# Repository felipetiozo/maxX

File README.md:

# maxX
Braço Robótico para fins educacionais
<div style="align=middle"></div>
<p align="center";> <b> Dia de testes do braço </b> </p>

# Divisões do projeto
* [`Software`](https://github.com/felipetiozo/maxX/tree/master/Software): Contem todas bibliotecas e código final do braço.
* [`Eletronica`](https://github.com/felipetiozo/maxX/tree/master/Eletronica): Possui todo esquema eletronico e o modelo final da PCB.
* [`Mecânica`](https://github.com/felipetiozo/maxX/tree/master/Mecanica): Todos arquivos .sldprt e .dxf do projeto.

## Eletronica
A PCB (Printed board circuit) do projeto foi construida no software [EAGLE(v8.3.1)](https://www.autodesk.com/products/eagle/overview) e fresada em uma mini cnc. [(Othermill)](https://www.bantamtools.com/)
### Lista de materiais 
| Qtd | Item | Loja | R$ |
|-----|------|-----|-----|
| 6 | MG995 Servo Motor | [Jsumo](http://www.jsumo.com/mg995-metal-gear-rc-servo-motor-towerpro) | 30,00 | 
| 1 | ATmega328P | [B.E](http://www.baudaeletronica.com.br/kit-arduino-atmega328p-bootloader.html) | 17,81 | 
| 2 | Encoder Decoder KY-040 | [Robocore](https://www.pololu.com/product/713) | 11,00 | 
| 1 | LCD 16x2 i2c | [Robocore](https://www.robocore.net/loja/produtos/lcd-16x2-5v-com-interface-i2c.html) | 49,00 | 
| 1 | FTDI Basic Breakout - 3.3V | [Sparkfun](https://www.sparkfun.com/products/9873) | 38,00 | 
| 2 | LM2596 | [B.E](http://www.baudaeletronica.com.br/modulo-regulador-de-tensao-lm2596.html) | 10,97 | 
| 1 | Fonte 12V 3A | [B.E](http://www.baudaeletronica.com.br/fonte-chaveada-12vdc-3a.html) | 48,37 | 

## Mecânica
O projeto mecânico foi desenvolvido no software de CAD [SolidWorks](http://www.solidworksbrasil.com.br/) e foi construido em 5 versões até chegar a final. Todas as peças foram impressas em 3D e cortadas em máquinas de corte a laser.

### Lista de materiais
| Qtd | Item | Loja | R$ |
|-----|------|-----|-----|
| 1 | Garra Robótica Croc | [Robocore](https://www.robocore.net/loja/produtos/garra-robotica-croc.html) | 29,00 | 
| 2 | Ball Caster with 3/8″ Metal Ball | [Pololu](https://www.pololu.com/product/951) | 6,50 | 

## Software
O software foi desenvolvido em cima da IDE [Arduino](https://www.arduino.cc/) e está dividido em diversas funções para uma utilização mais fácil.

# Contribuidores

<div style="align=middle"></div>
<p align="center";> <b> Participantes do grupo </b> </p>

* [Felipe Tiozo](https://github.com/felipetiozo)
* [Igor Sousa](https://www.linkedin.com/in/igorsousa/)
* [Guilherme Basilio](https://www.facebook.com/guilherme.basilio.969)
* [Carlos Lima](https://www.facebook.com/profile.php?id=100004150566418)

## Agradecimentos
* [Engenhoteca](http://engenhoteca.com.br/)
* [João Pedro](https://github.com/joaopedrovbs)
* [Felipe Silva](https://github.com/feosilva)
* [Marcos Oliveira](https://github.com/marcosdeoliveira)
* [Tenda Digital](http://tenda.digital/)

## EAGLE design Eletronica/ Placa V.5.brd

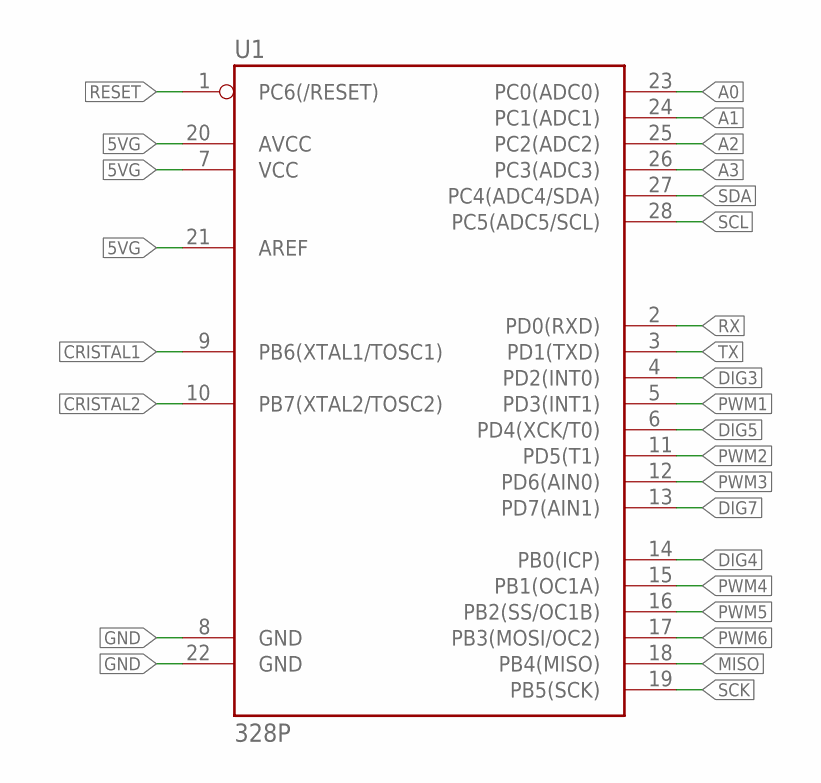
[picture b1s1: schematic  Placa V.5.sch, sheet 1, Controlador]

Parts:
U1: 328P; DIP28

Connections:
5VG: U1.7 (VCC), U1.20 (AVCC), U1.21 (AREF); also elsewhere on the board
A0: U1.23 (PC0(ADC0)); also elsewhere on the board
A1: U1.24 (PC1(ADC1)); also elsewhere on the board
A2: U1.25 (PC2(ADC2)); also elsewhere on the board
A3: U1.26 (PC3(ADC3)); also elsewhere on the board
CRISTAL1: U1.9 (PB6(XTAL1/TOSC1)); also elsewhere on the board
CRISTAL2: U1.10 (PB7(XTAL2/TOSC2)); also elsewhere on the board
DIG3: U1.4 (PD2(INT0)); also elsewhere on the board
DIG4: U1.14 (PB0(ICP)); also elsewhere on the board
DIG5: U1.6 (PD4(XCK/T0)); also elsewhere on the board
DIG7: U1.13 (PD7(AIN1)); also elsewhere on the board
GND: U1.8 (GND), U1.22 (GND); also elsewhere on the board
MISO: U1.18 (PB4(MISO))
PWM1: U1.5 (PD3(INT1)); also elsewhere on the board
PWM2: U1.11 (PD5(T1)); also elsewhere on the board
PWM3: U1.12 (PD6(AIN0)); also elsewhere on the board
PWM4: U1.15 (PB1(OC1A)); also elsewhere on the board
PWM5: U1.16 (PB2(SS/OC1B)); also elsewhere on the board
PWM6: U1.17 (PB3(MOSI/OC2)); also elsewhere on the board
RESET: U1.1 (PC6(/RESET)); also elsewhere on the board
RX: U1.2 (PD0(RXD)); also elsewhere on the board
SCK: U1.19 (PB5(SCK)); also elsewhere on the board
SCL: U1.28 (PC5(ADC5/SCL)); also elsewhere on the board
SDA: U1.27 (PC4(ADC4/SDA)); also elsewhere on the board
TX: U1.3 (PD1(TXD)); also elsewhere on the board

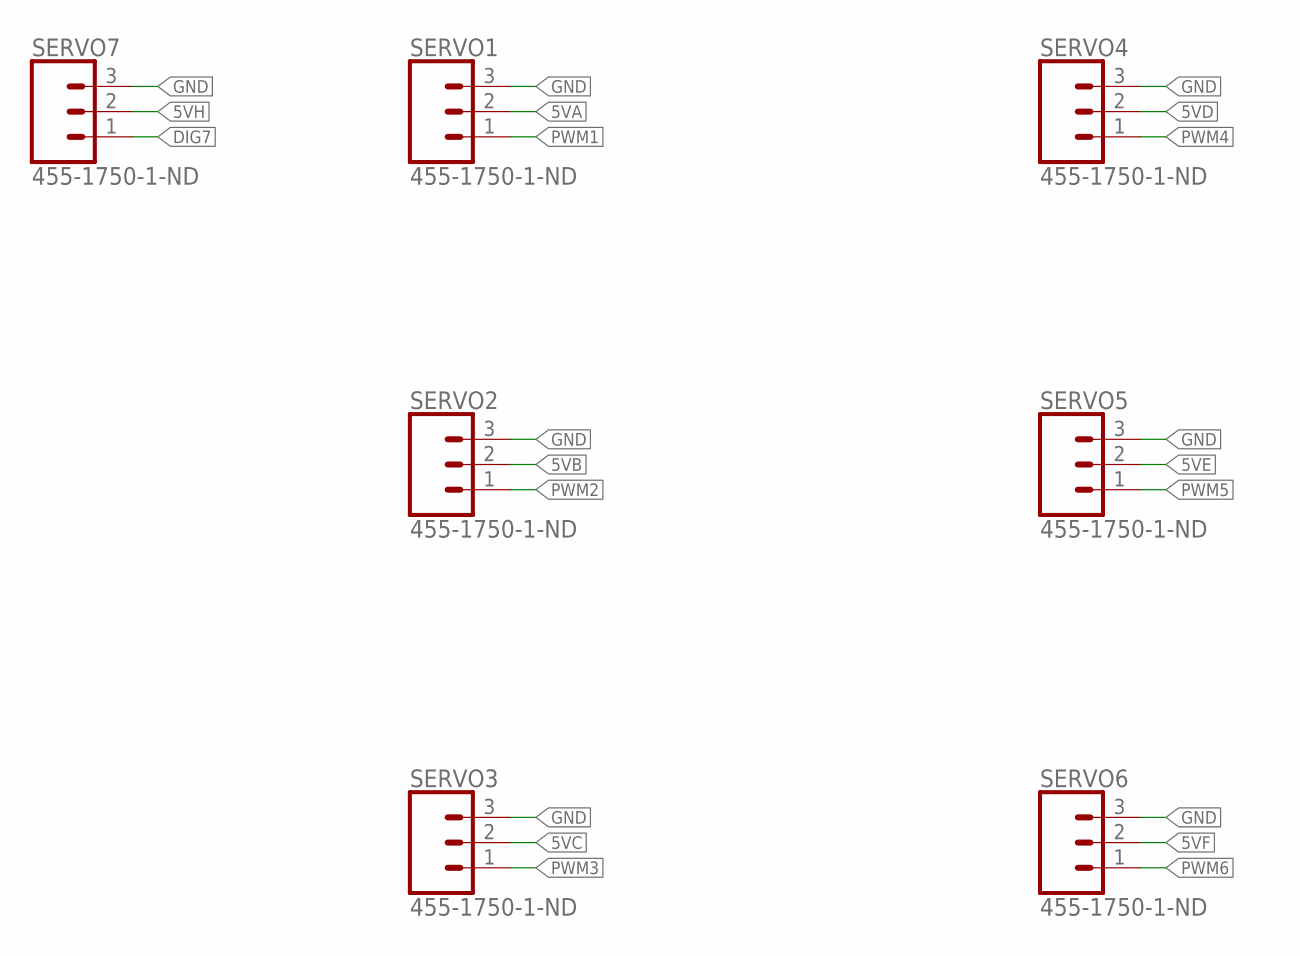
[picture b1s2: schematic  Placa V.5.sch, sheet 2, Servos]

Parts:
SERVO1, SERVO2, SERVO3, SERVO4, SERVO5, SERVO6, SERVO7: 455-1750-1-ND; 1X03

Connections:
5VA: SERVO1.2; also elsewhere on the board
5VB: SERVO2.2; also elsewhere on the board
5VC: SERVO3.2; also elsewhere on the board
5VD: SERVO4.2; also elsewhere on the board
5VE: SERVO5.2; also elsewhere on the board
5VF: SERVO6.2; also elsewhere on the board
5VH: SERVO7.2; also elsewhere on the board
DIG7: SERVO7.1; also elsewhere on the board
GND: SERVO1.3, SERVO2.3, SERVO3.3, SERVO4.3, SERVO5.3, SERVO6.3, SERVO7.3; also elsewhere on the board
PWM1: SERVO1.1; also elsewhere on the board
PWM2: SERVO2.1; also elsewhere on the board
PWM3: SERVO3.1; also elsewhere on the board
PWM4: SERVO4.1; also elsewhere on the board
PWM5: SERVO5.1; also elsewhere on the board
PWM6: SERVO6.1; also elsewhere on the board

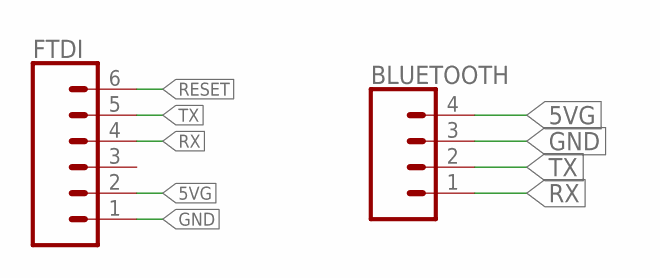
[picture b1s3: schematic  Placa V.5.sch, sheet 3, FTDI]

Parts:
BLUETOOTH: CONN_04; 1X04
FTDI: CONN_06SILK_FEMALE_PTH; 1X06

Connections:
5VG: BLUETOOTH.4, FTDI.2; also elsewhere on the board
GND: BLUETOOTH.3, FTDI.1; also elsewhere on the board
RESET: FTDI.6; also elsewhere on the board
RX: BLUETOOTH.1, FTDI.4; also elsewhere on the board
TX: BLUETOOTH.2, FTDI.5; also elsewhere on the board

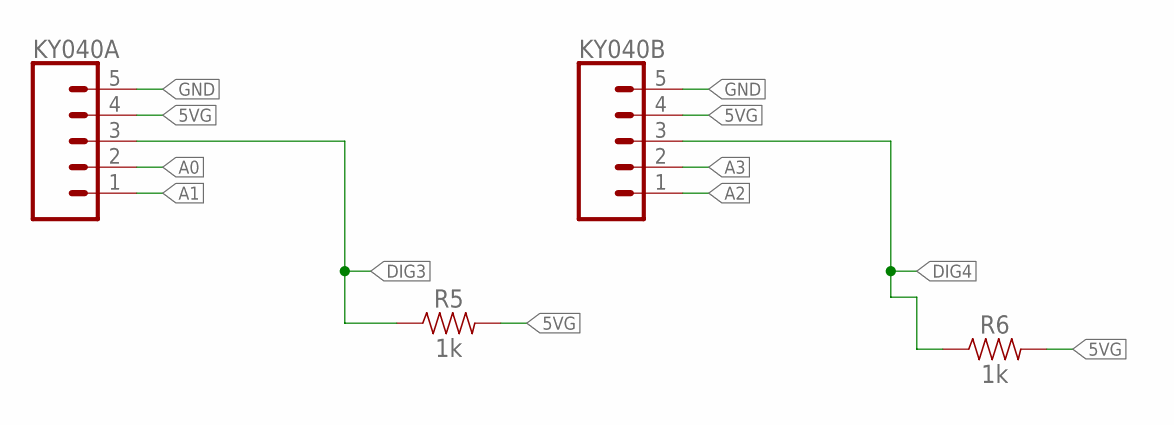
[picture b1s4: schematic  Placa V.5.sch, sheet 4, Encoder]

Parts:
KY040A, KY040B: CONN_05; 1X05
R5, R6: 1k; AXIAL-0.3

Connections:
5VG: KY040A.4, KY040B.4, R5.P$2 (2), R6.P$2 (2); also elsewhere on the board
A0: KY040A.2; also elsewhere on the board
A1: KY040A.1; also elsewhere on the board
A2: KY040B.1; also elsewhere on the board
A3: KY040B.2; also elsewhere on the board
DIG3: KY040A.3, R5.P$1 (1); also elsewhere on the board
DIG4: KY040B.3, R6.P$1 (1); also elsewhere on the board
GND: KY040A.5, KY040B.5; also elsewhere on the board

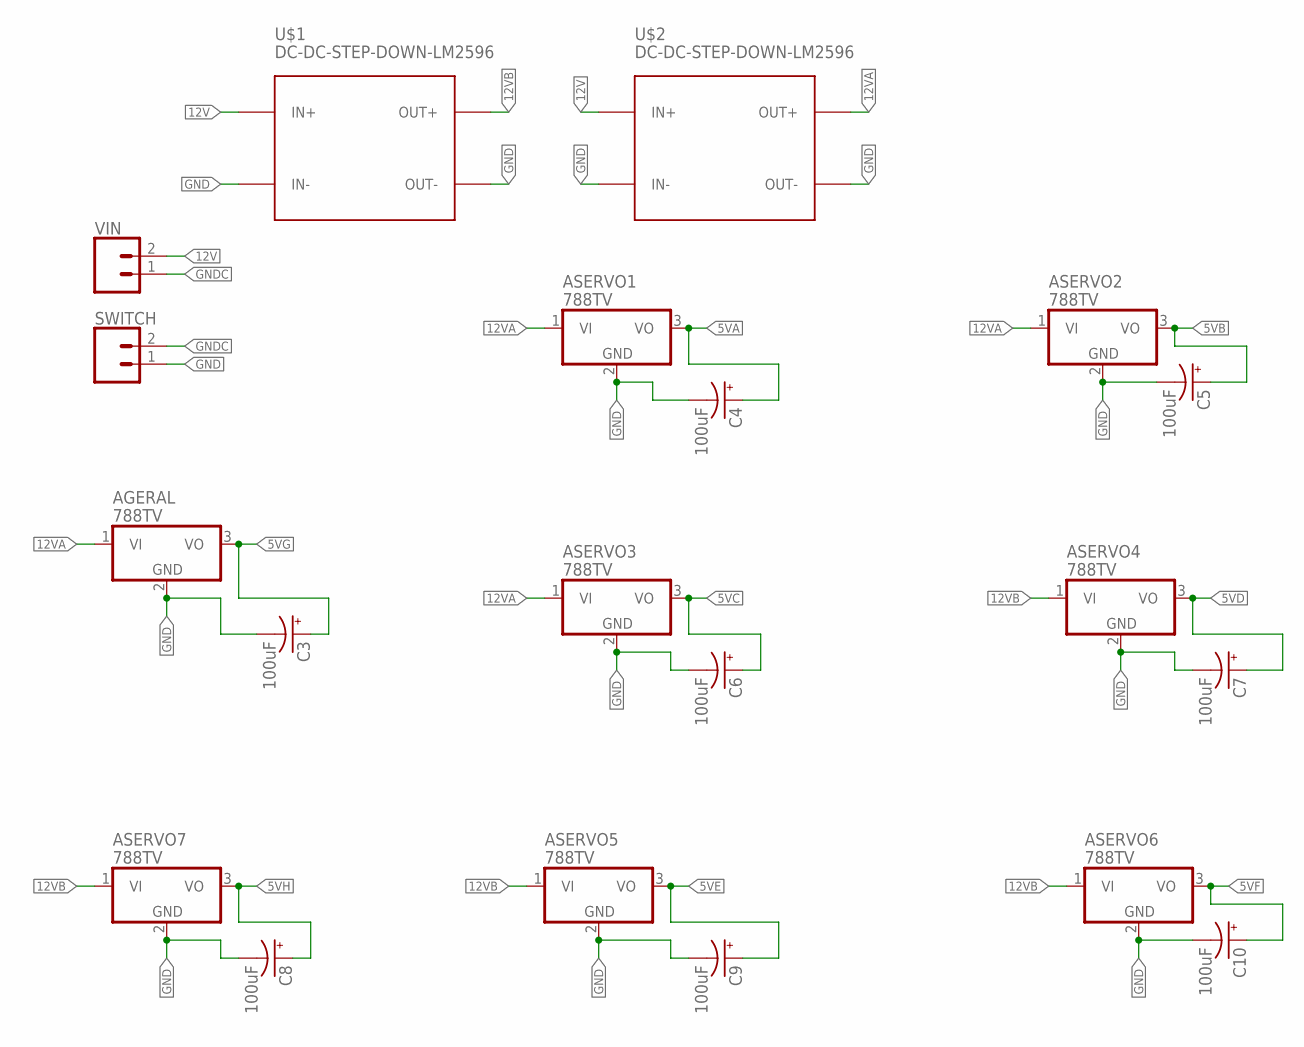
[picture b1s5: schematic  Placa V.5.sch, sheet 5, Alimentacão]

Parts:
AGERAL: 788TV; TO220V
ASERVO1, ASERVO2, ASERVO3, ASERVO4, ASERVO5, ASERVO6, ASERVO7: 788TV; TO220V
C3, C4, C5, C6, C7, C8, C9, C10: 100uF; CPOL-RADIAL-2.5MM-6.5MM
SWITCH: CONN_02; 1X02
U$1, U$2: DC-DC-STEP-DOWN-LM2596
VIN: CONN_02; 1X02

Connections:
5VA: ASERVO1.3 (VO), C4.1 (+); also elsewhere on the board
5VB: ASERVO2.3 (VO), C5.1 (+); also elsewhere on the board
5VC: ASERVO3.3 (VO), C6.1 (+); also elsewhere on the board
5VD: ASERVO4.3 (VO), C7.1 (+); also elsewhere on the board
5VE: ASERVO5.3 (VO), C9.1 (+); also elsewhere on the board
5VF: ASERVO6.3 (VO), C10.1 (+); also elsewhere on the board
5VG: AGERAL.3 (VO), C3.1 (+); also elsewhere on the board
5VH: ASERVO7.3 (VO), C8.1 (+); also elsewhere on the board
12V: U$1.IN+, U$2.IN+, VIN.2
12VA: AGERAL.1 (VI), ASERVO1.1 (VI), ASERVO2.1 (VI), ASERVO3.1 (VI), U$2.OUT+
12VB: ASERVO4.1 (VI), ASERVO5.1 (VI), ASERVO6.1 (VI), ASERVO7.1 (VI), U$1.OUT+
GND: AGERAL.2 (GND), ASERVO1.2 (GND), ASERVO2.2 (GND), ASERVO3.2 (GND), ASERVO4.2 (GND), ASERVO5.2 (GND), ASERVO6.2 (GND), ASERVO7.2 (GND), C3.2 (-), C4.2 (-), C5.2 (-), C6.2 (-), C7.2 (-), C8.2 (-), C9.2 (-), C10.2 (-), SWITCH.1, U$1.IN-, U$1.OUT-, U$2.IN-, U$2.OUT-; also elsewhere on the board
GNDC: SWITCH.2, VIN.1

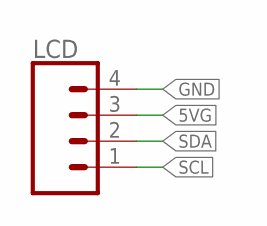
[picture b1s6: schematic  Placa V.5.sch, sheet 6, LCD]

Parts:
LCD: CONN_04; 1X04

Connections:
5VG: LCD.3; also elsewhere on the board
GND: LCD.4; also elsewhere on the board
SCL: LCD.1; also elsewhere on the board
SDA: LCD.2; also elsewhere on the board

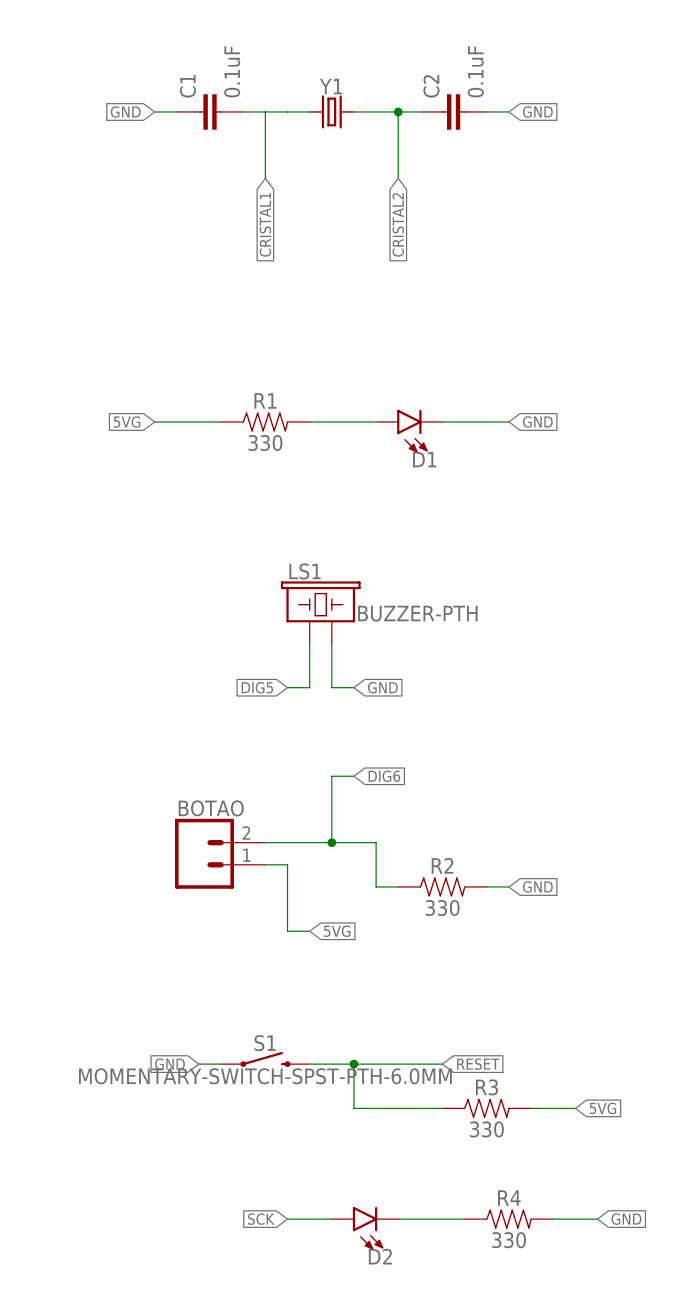
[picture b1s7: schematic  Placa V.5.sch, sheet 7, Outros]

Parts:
BOTAO: CONN_02; 1X02
C1, C2: 0.1uF; CAP-PTH-SMALL-KIT
D1, D2: LED5MM; LED_5MM
LS1: BUZZER-PTH; BUZZER-12MM
R1, R2, R3, R4: 330; AXIAL-0.3
S1: MOMENTARY-SWITCH-SPST-PTH-6.0MM; TACTILE_SWITCH_PTH_6.0MM
Y1: CRYSTALPTH-HC49US; HC49US

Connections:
5VG: BOTAO.1, R1.P$1 (1), R3.P$2 (2); also elsewhere on the board
CRISTAL1: C1.2, Y1.1; also elsewhere on the board
CRISTAL2: C2.1, Y1.2; also elsewhere on the board
DIG5: LS1.+ (1); also elsewhere on the board
DIG6: BOTAO.2, R2.P$1 (1)
GND: C1.1, C2.2, D1.K (C), LS1.- (2), R2.P$2 (2), R4.P$2 (2), S1.1; also elsewhere on the board
unnamed: D1.A, R1.P$2 (2)
unnamed: D2.K (C), R4.P$1 (1)
RESET: R3.P$1 (1), S1.3 (2); also elsewhere on the board
SCK: D2.A; also elsewhere on the board

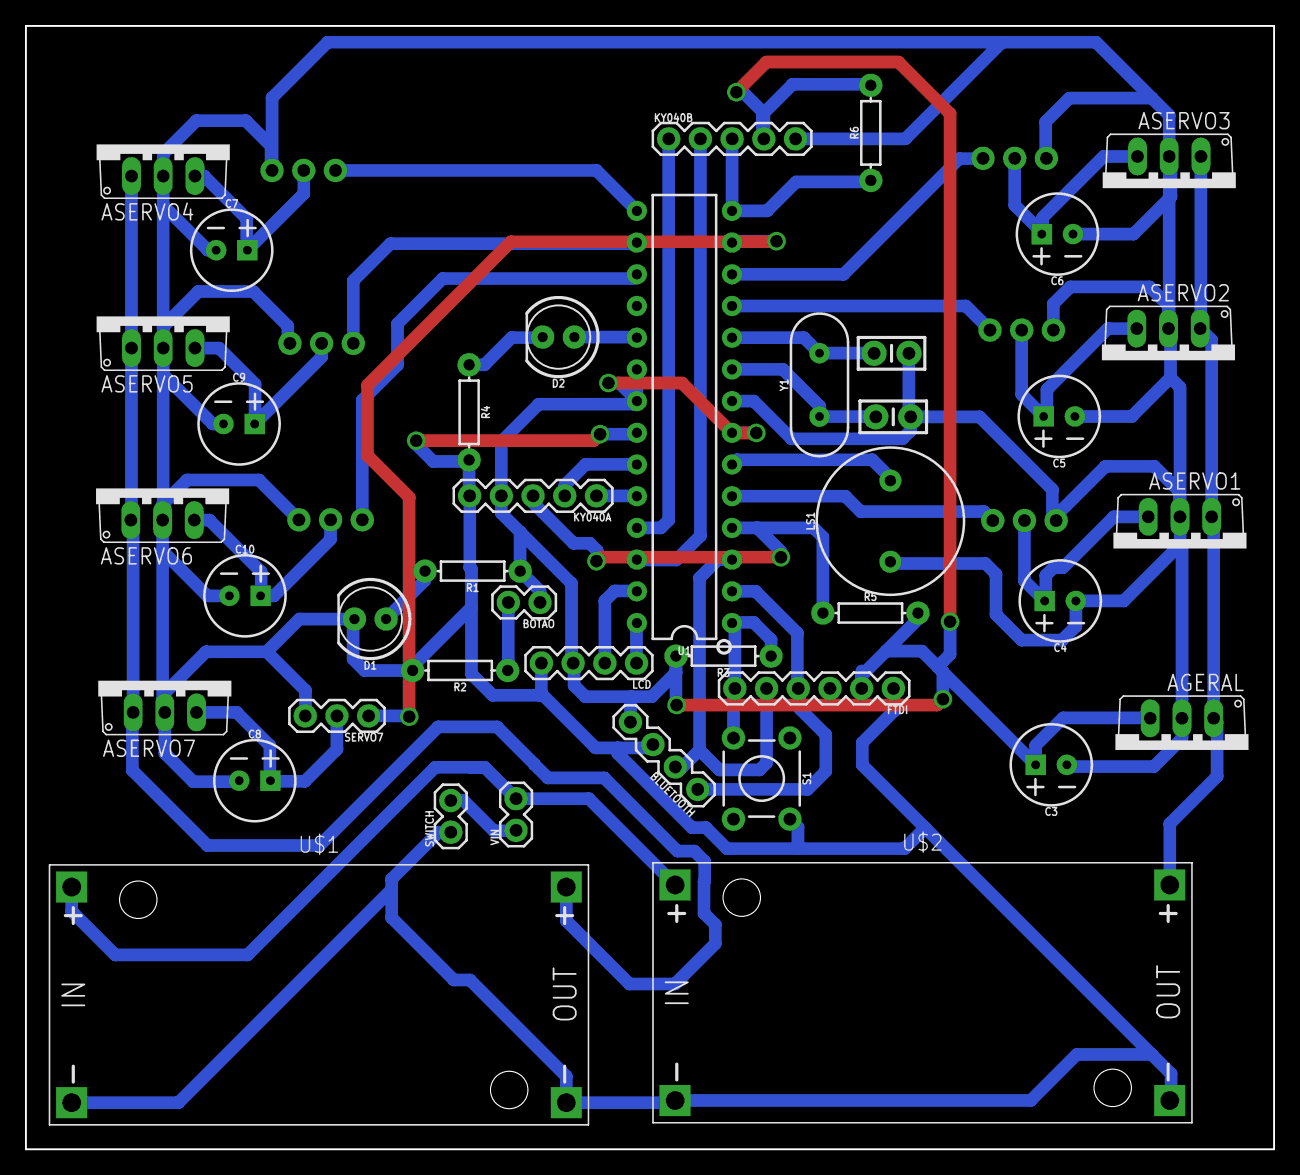
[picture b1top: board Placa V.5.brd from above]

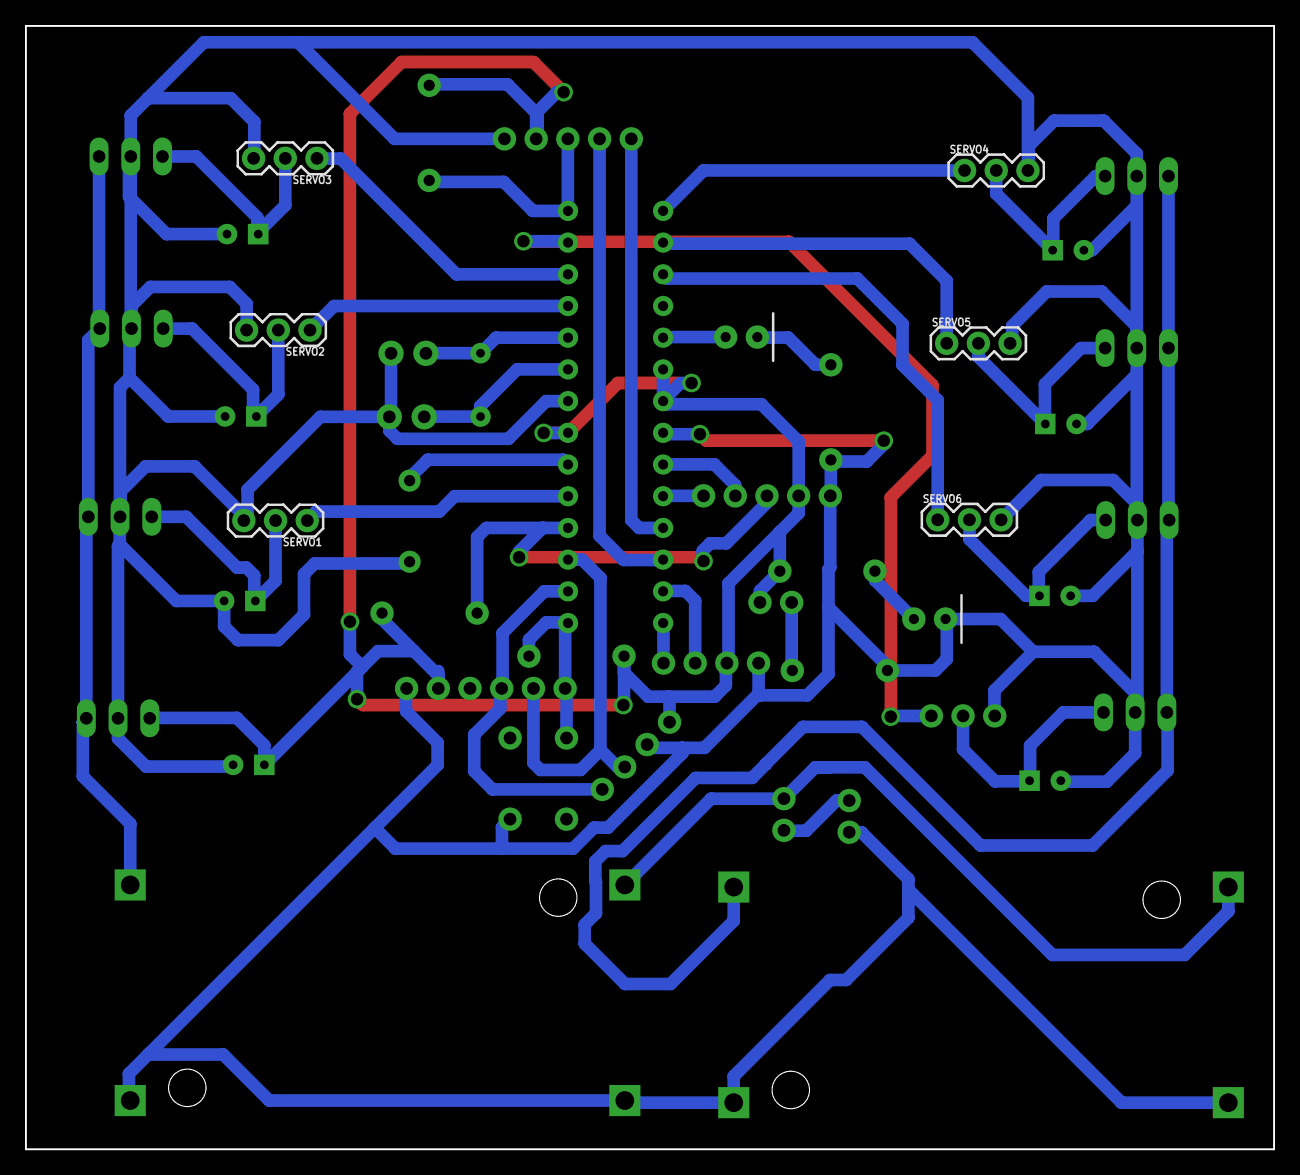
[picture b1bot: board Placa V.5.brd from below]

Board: 2 copper layers, 100.0 x 90.0 mm, 47 parts (6 on the bottom side), 38 nets.

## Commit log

2017-11-27 Testing some commands
2017-11-27 Add maxx PCB
2017-11-27 Added maxX photo
2017-11-28 Added new functions and demo mode
2017-11-28 Added some new functions
2017-11-29 README updated.
2017-11-29 Test
2017-11-29 Rename photos
2017-11-29 Readme update
2017-11-29 Added mechanical files
2017-11-29 Added some changes
2017-11-30 README changes
2018-08-12 fix some titles
2018-08-12 fix image on readme

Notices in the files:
parts and their libraries:
SparkFun-Connectors: Licensing: Creative Commons ShareAlike 4.0 International - https://creativecommons.org/licenses/by-sa/4.0
diy-modules: Released under the Creative Commons Attribution 4.0 International License: http://creativecommons.org/licenses/by/4.0
